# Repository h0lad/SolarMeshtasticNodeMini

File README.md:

# What is this thing?

This is a miniaturized version of the [SolarMeshtasticNode](https://github.com/h0lad/SolarMeshtasticNode).

Specs are the same - with following things removed:
 - 18650 LiPo case
 - ADC circuit for VBUS
 - LEDs 

It's fully Meshtastic and Meshcore compatible.

## Physical size

37mm x 47mm

It should *theoretically* fit into this [AliExpress Box: 83x58x34](https://de.aliexpress.com/item/1005005480970197.html) with a little bit of spare space for a through-hole SMA<->U.FL connector.

## Hardware Verification

PCB not tested - but inherited from tested SolarMeshtasticNode.

 ## License

CERN OHL v2 – Strongly Reciprocal (S)

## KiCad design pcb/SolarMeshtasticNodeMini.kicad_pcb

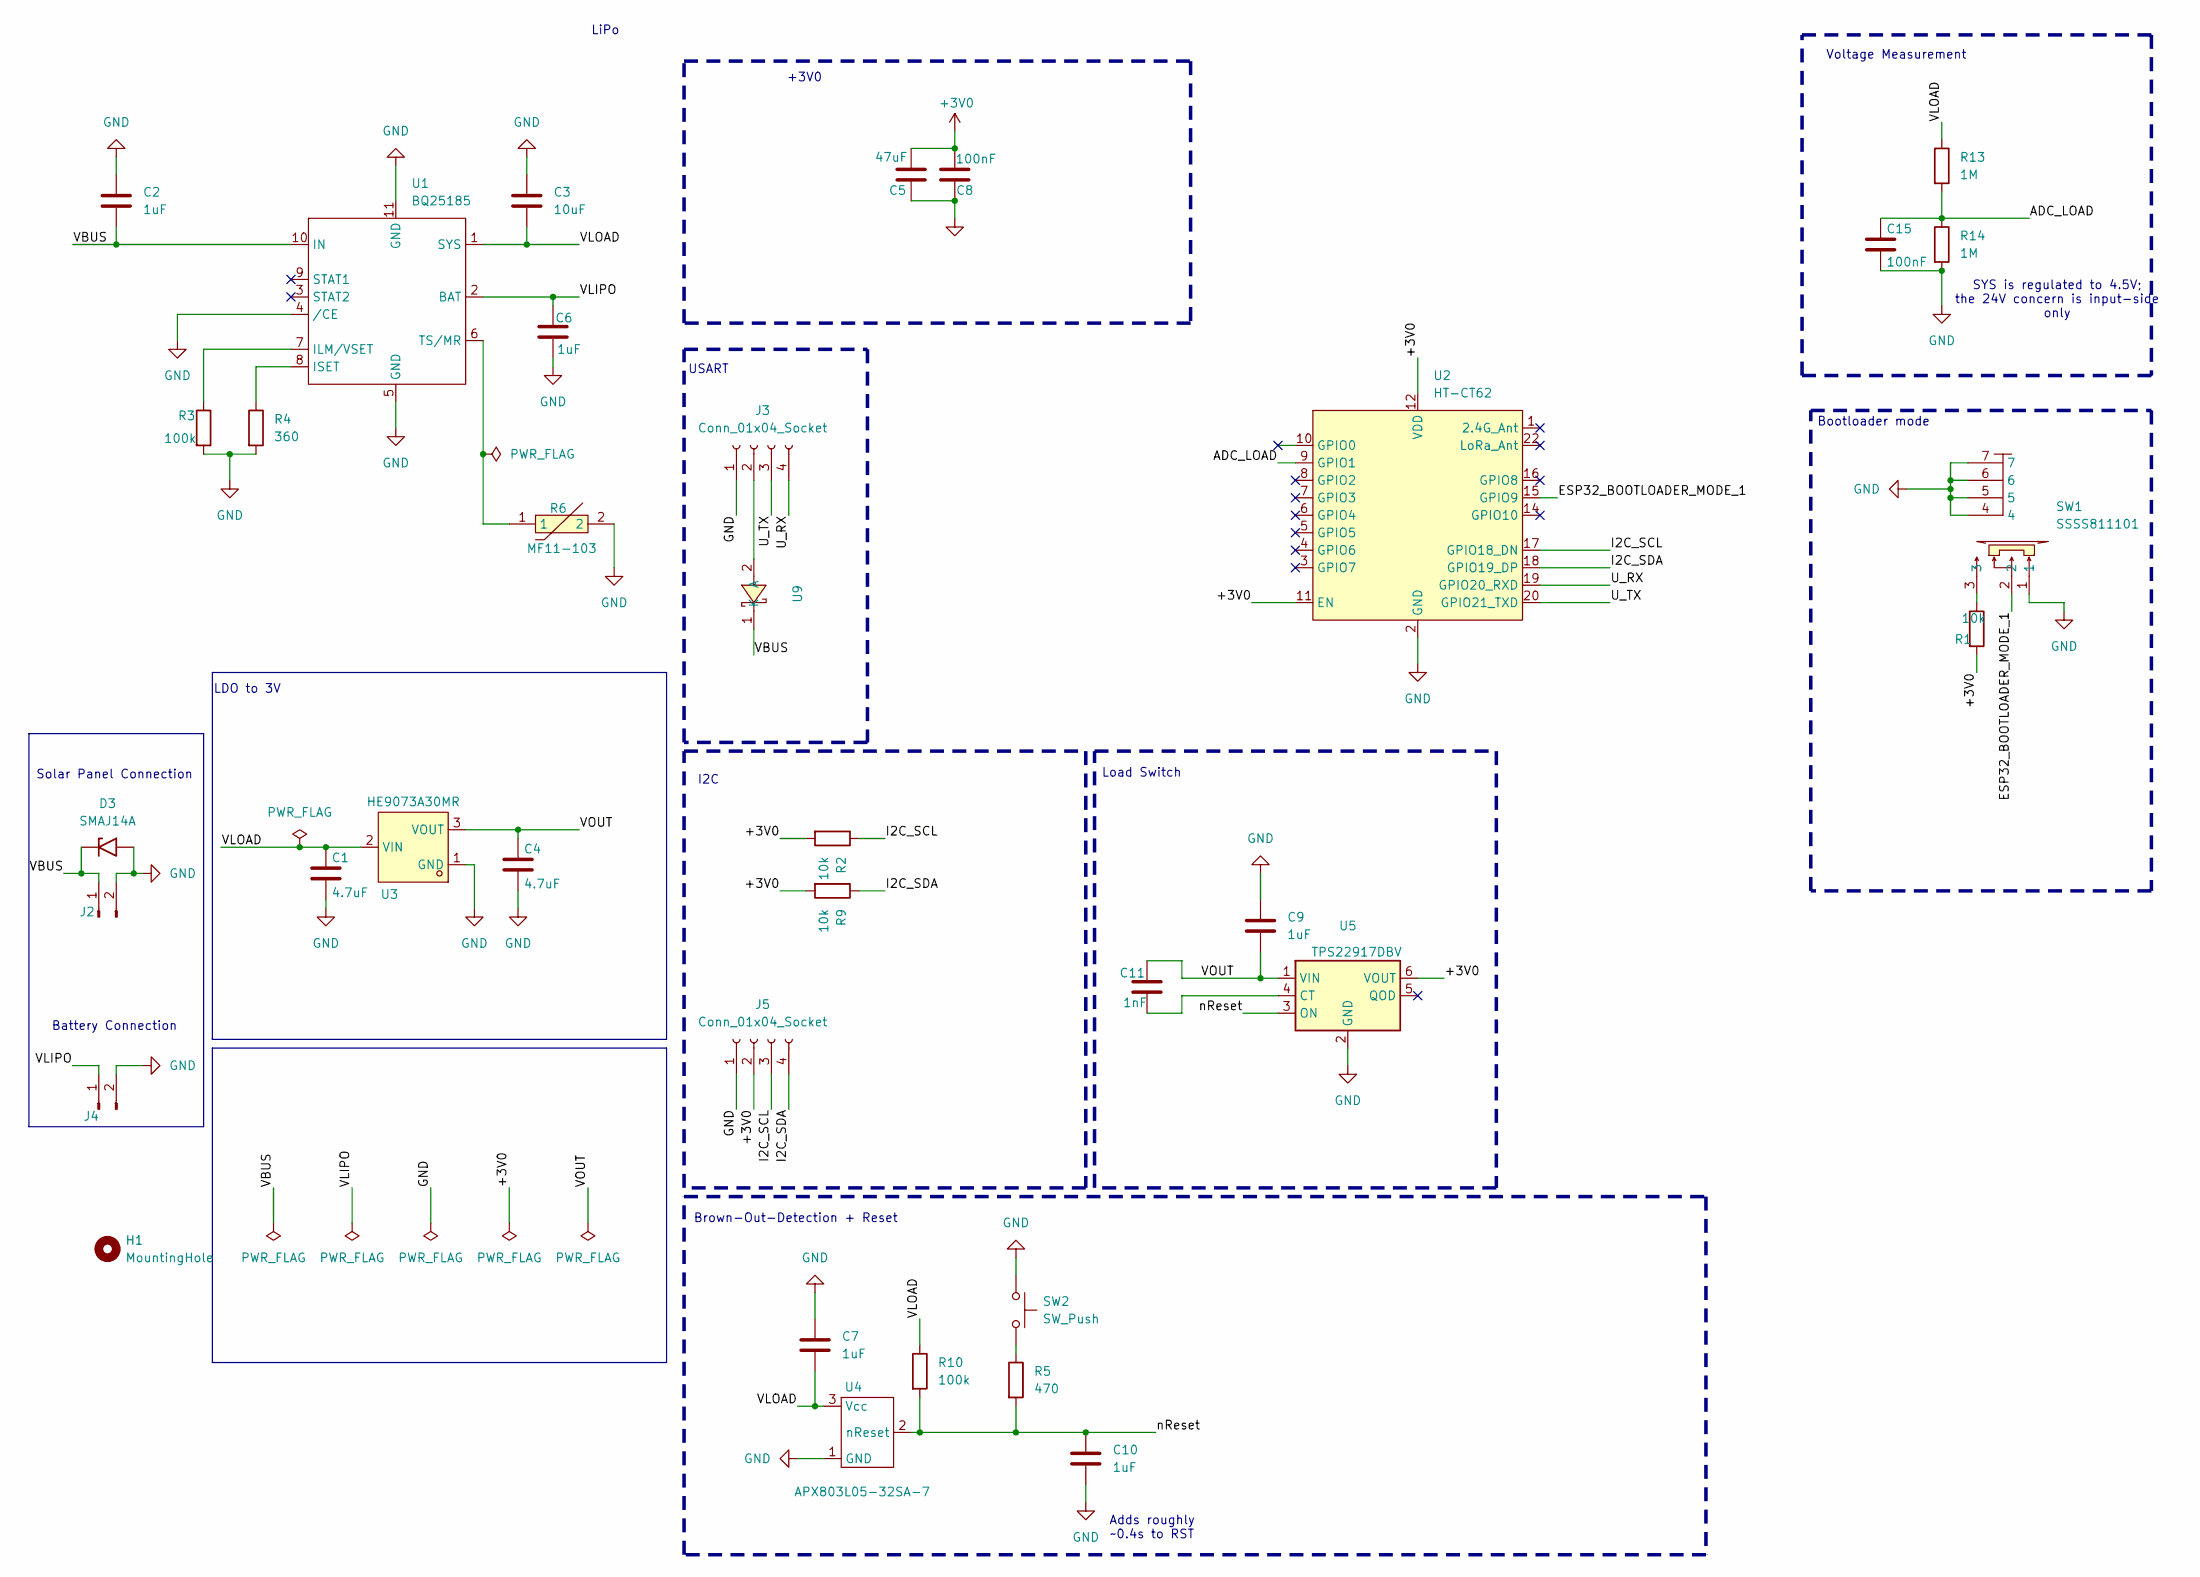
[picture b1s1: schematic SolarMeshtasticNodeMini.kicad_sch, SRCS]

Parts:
C1, C4: 4.7uF; C_0805_2012Metric_Pad1.18x1.45mm_HandSolder
C2, C6, C9, C10: 1uF; C_0805_2012Metric_Pad1.18x1.45mm_HandSolder
C3: 10uF; C_0805_2012Metric_Pad1.18x1.45mm_HandSolder
C5: 47uF; R_1206_3216Metric_Pad1.30x1.75mm_HandSolder
C7: 1uF; C_1206_3216Metric_Pad1.33x1.80mm_HandSolder
C8, C15: 100nF; C_0805_2012Metric_Pad1.18x1.45mm_HandSolder
C11: 1nF; C_0805_2012Metric_Pad1.18x1.45mm_HandSolder
D3: SMAJ14A; D_SMA
H1: MountingHole; MountingHole_2.7mm_M2.5_ISO7380
J2: Conn_01x02_Socket; JST_PH_B2B-PH-K_1x02_P2.00mm_Vertical
J3, J5: Conn_01x04_Socket; JST_PH_B4B-PH-K_1x04_P2.00mm_Vertical
J4: Conn_01x02_Pin; JST_PH_B2B-PH-K_1x02_P2.00mm_Vertical
R1, R2, R9: 10k; R_0805_2012Metric_Pad1.20x1.40mm_HandSolder
R3, R10: 100k; R_0805_2012Metric_Pad1.20x1.40mm_HandSolder
R4: 360; R_0805_2012Metric_Pad1.20x1.40mm_HandSolder
R5: 470; R_0805_2012Metric_Pad1.20x1.40mm_HandSolder
R6: MF11-103; R_0805_2012Metric_Pad1.20x1.40mm_HandSolder; LCSC Part C70913
R13, R14: 1M; R_0805_2012Metric_Pad1.20x1.40mm_HandSolder
SW1: SSSS811101; SW-SMD_SSSS811101; LCSC Part C109335
SW2: SW_Push; SMA_L4.3-W2.6-LS5.1-RD
U1: BQ25185; SON40P220X200X80-11N
U2: HT-CT62; Heltec_HT-CT62
U3: HE9073A30MR; SOT-23-3_L2.9-W1.6-P1.90-LS2.8-BR-CW; LCSC Part C723793
U4: APX803L05-32SA-7; SOT23-3
U5: TPS22917DBV; SOT-23-6
U9: SS26_C5350986; SMA_L4.3-W2.6-LS5.1-RD; LCSC Part C5350986

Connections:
+3V0: C5.2, C8.2, J5.2, R1.2, R2.2, R9.2, U2.11 (EN), U2.12 (VDD), U5.6 (VOUT)
/ADC_LOAD: C15.1, R13.2, R14.1, U2.9 (GPIO1)
/ESP32_BOOTLOADER_MODE_1: SW1.2, U2.15 (GPIO9)
/I2C_SCL: J5.3, R2.1, U2.17 (GPIO18_DN)
/I2C_SDA: J5.4, R9.1, U2.18 (GPIO19_DP)
/U_RX: J3.4, U2.19 (GPIO20_RXD)
/U_TX: J3.3, U2.20 (GPIO21_TXD)
/VBUS: C2.2, D3.1 (A1), J2.1, U1.10 (IN), U9.1 (K)
/VLIPO: C6.1, J4.1, U1.2 (BAT)
/VLOAD: C1.1, C3.2, C7.2, R10.1, R13.1, U1.1 (SYS), U3.2 (VIN), U4.3 (Vcc)
/VOUT: C4.1, C9.1, C11.1, U3.3 (VOUT), U5.1 (VIN)
/nReset: C10.2, R5.2, R10.2, U4.2 (nReset), U5.3 (ON)
GND: C1.2, C2.1, C3.1, C4.2, C5.1, C6.2, C7.1, C8.1, C9.2, C10.1, C15.2, D3.2 (A2), J2.2, J3.1, J4.2, J5.1, R3.2, R4.2, R6.2, R14.2, SW1.1, SW1.4, SW1.5, SW1.6, SW1.7, SW2.1, U1.4 (/CE), U1.5 (GND), U1.11 (GND), U2.2 (GND), U2.13 (GND), U2.21 (GND), U3.1 (GND), U4.1 (GND), U5.2 (GND)
unnamed: J3.2, U9.2 (A)
unnamed: R1.1, SW1.3
unnamed: R5.1, SW2.2
unnamed: R3.1, U1.7 (ILM/VSET)
unnamed: R4.1, U1.8 (ISET)
unnamed: R6.1, U1.6 (TS/MR)
unnamed: C11.2, U5.4 (CT)

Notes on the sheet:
Bootloader mode
Adds roughly ~0.4s to RST
USART
Voltage Measurement
LiPo
+3V0
Brown-Out-Detection + Reset
Solar Panel Connection
LDO to 3V
I2C
Battery Connection
SYS is regulated to 4.5V; the 24V concern is input-side only
Load Switch

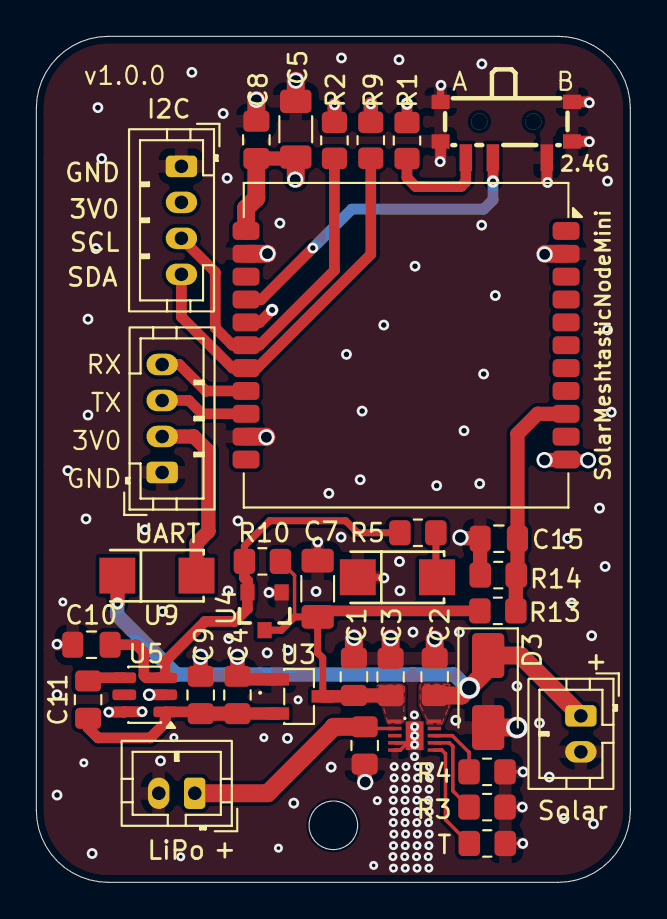
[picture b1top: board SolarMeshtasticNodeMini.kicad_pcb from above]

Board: 4 copper layers, 33.0 x 47.0 mm, 36 parts (0 on the bottom side), 20 nets.

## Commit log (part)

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2026-01-08 schematic: initial commit
2026-01-08 pcb, sch: first layout done
2026-01-08 pcb: fix some missing .steps and move silk prints around
2026-01-08 pcb, sch: use VLOAD and not VBUS for ADC
2026-01-08 docs, README: initial commit
2026-01-08 README: add size
2026-01-08 README: be more precise regarding the modifications
2026-01-08 pcb, jpg: small eyecandy works
2026-01-08 README: remove duplications
2026-01-08 pcb: add missing silk prints
2026-01-10 pcb, sch: add mounting hole (M2.5)
2026-01-10 pcb, sch: other hole size and re-center
2026-01-11 pcb: mark 2.4GHz u.fl connector with a silk print
2026-01-11 README: add some more informations
2026-01-11 README: be more precise about the though-hole connector
2026-01-11 pcb,sch: make the 3v3 of the bootloader switch weaker
2026-01-11 pcb: optimize 3v3 and gnd rails a bit
2026-01-16 pcb, sch: add load switch to control entire 3.3V rail
    Until now only the ESP32 was disabled if the voltage drops due to
    discharge. This might cause the sensors to slip into a slow brown-out.
2026-01-16 pcb, sch: replace reset ic with TI TPS3890 to get rid of bouncing behaviour
